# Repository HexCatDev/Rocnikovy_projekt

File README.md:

# Ročníkový projekt S3E Dobeš Tomáš Digitální hodiny
## Zvláštní poděkování
Zvláště bych chtěl poděkovat panu Miroslavu Máchovi za rady a pomoc při výběru součástek a řešení problémů konstrukčního typu.
A také  panu Jiřímu Vinterovi za rady a kontakty.

## To-do list
- [x] Navrhnout schéma 
- [x] Objednat součástky
- [x] Otestovat na breadboardu
- [x] Navrhnout PCB
- [x] Vyrobit PCB osadit, otestovat

## Princip a popis
Původní myšlenka jak zhotovit tento obvod byla, že by se jednotlivé výstupy na zobrazovače připojily přes posuvné registry, ovšem bylo by jich zapotřebí 6 kousků (HH:mm:ss) převod časového údaje z RTC by bylo zhotoveno přímo v PIC.

Po konzultaci s panem Máchou by bylo lepší Multiplexovat číslice 1:6 tzn. že v jednom okamžiku problikne jeden segment, takto se "probliká" každý segment zvlášť v určité rychlosti(Hz), od určité rychlosti ± 30 Hz se obraz jeví jako spojitý.[1]
### Blokové schéma

<figure>
  
  <figcaption align="center"><i>Obrázek 1: Blokové schéma zapojení hodin</i></figcaption>
</figure>

### Součástky a jejich funkce v obvodu
V této podkapitole budou popsány hlavně podstatné součástky RTC, PIC, tranzistorové pole a samotné tranzistory (touto částí obvodu se chápe zobrazovací část. Vzhledem ke složitosti projektu zde nebude popsáno jak každý samostatný prvek funguje. 

- Obecné informace na vstupu napětí jsou  umístěny tzv. Tank Capacitors[2, kap. 4.2.2], jsou to dva kondenzátory 100uF/35V na napájení jejich funkce zajišťuje stabilní napětí při náhlém zvětšení proudového zatížení. Každý IO napájený z VCC má připojený tzv. Decoupling Capacitors[10] tyto kondenzátory mají na starosti odrušení od možných na indukovaných vysokých frekvencí, všechny mají hodnotu 100nF. Dále je v obvodu implementována dioda která obvod chrání před přepólováním její úbytek je ± 1100mV[11], takže velikost napájecího napětí bude 6V (6-1 = 5V) maximální napětí všech IO je 5,5V. Před vyrobením PCB bude zdroj otestován na stabilitu napětí.

- Mozkem obvodu je PIC18F47Q43-I-P[2] má na starosti komunikaci s RTC, multiplexování a řízení hodin. 

- RTC (Real Time Clock)[3] a Krystal[4] 
Tento IO komunikuje pomocí I2C protokolu s PIC a poskytuje časový údaj tento údaj je poskytován v dekadickém formátu. Má také externí zdroj oscilací krystal o frekvenci 32 768 Hz tato hodnota je definovaná v jeho dokumentaci[3, kap. 4.2.1]. Doporučená hodnota kondenzátorů které slouží jako kapacitní zátěž je 20pF.[3, kap. 4.2.1] Kondenzáty byly zapojeny podle doporučeného zapojení v citaci 3 kapitole FIGURE 4-3[3, kap. FIGURE 4-3].

- Tranzistorové pole ULN2804A[5] tento IO ve svém pouzdře DIP 18 obsahuje 8x NPN transistorů se spol. emitorem s max. kolektorovím  proudem 0,5A a max. napětím mezi kolektorem a emitorem 50V tento IO slouží pro výběr segmentu který bude svítit (A-DP)

- 7 Segmentové zobrazovače[6][7] 2x 20,32mm a 2x 10mm se společnou katodou obsahují 16x znaků v pouzdře 2x8 (7+DP) jsou připojeny na přes rezistory na ULN2804A[5] a jednotlivé znaky jsou připojeny přes tranzistory DTA123JCA[8] které uzemňují daný znak.

- tranzistory IRLML5203 SMD[8] P-MOSFET Uds max. 30V Ic 3A P 1.25W tyto tranzistory zajišťují spojení daného segmentu s napětím VCC tzn. pokud bude na 1. digitu svítit znak "A" ULN2804A[5] přivede na pin A napětí a poté tranzistor sepne a tím přivede na anodu proud poteče přes segmenty které jsou uzemněné a v důsledku toho se rozsvítí.

Video: https://youtu.be/Hi3HrBMFoAA

## Návrh schéma a PCB
- návrh schéma byl konzultován s panem Máchou a také byl upravován v souladu s dokumentací jednotlivých součástek s jejich doporučeními.

<figure>
  
  <figcaption align="center"><i>Obr. 1.: Schéma zapojení</i></figcaption>
</figure>

  <figcaption align="center"><i>Obr. 2: Schéma zapojení</i></figcaption>
</figure>

  <figcaption align="center"><i>Obr. 3: Schéma zapojení</i></figcaption>
</figure>

<figure>
  
  <figcaption align="center"><i>Obr. 5: Neosazená PCB deska z horní strany strany</i></figcaption>
</figure>

<figure>
  
  <figcaption align="center"><i>Obrázek 7: Neosazená PCB deska ze spodní strany</i></figcaption>
</figure>

## Komponenty použité v projektu
- Aktivní součástky
	+ MCU https://ecom.cz/eshop/detail/73426-PIC18F47Q43-I-P
	+ RTC https://ecom.cz/eshop/detail/39997-MCP7940M-I-SN
	+ T. pole https://ecom.cz/eshop/detail/5723-ULN2804A
	+ Tranzistory SMD https://ecom.cz/eshop/detail/80941
	+ Dioda SMD https://ecom.cz/eshop/detail/82063-M7-SMD-T-R
- Krystal
	+ Crystal https://www.tme.eu/cz/details/32.768k-38-sr/krystalove-rezonatory-tht/sr-passives/32-768k-3-8-sr/
- Headry:
	+ 2X https://ecom.cz/eshop/detail/84648
	+ 5X https://ecom.cz/eshop/detail/84654
- Patice
	+ SIL 1X5 https://ecom.cz/eshop/detail/85256
  + SIL 1X9 https://ecom.cz/eshop/detail/85261
  + DIP 18 https://ecom.cz/eshop/detail/64634-DIL-18-3-NT-1
  + DIP 40 https://ecom.cz/eshop/detail/64639-DIL-40-6-YT-1
- Zobrazovače
	+ 7 segment 2X 20,32mm: https://ecom.cz/eshop/detail/29807-LD-FYD-8021DUHR-21
	+ 7 segment 10mm: https://ecom.cz/eshop/detail/29798-LD-FYD-3921BUHR-21
- Pasivní součástky
	+ Rezistory a Kondenzátory
		* 4K7 https://ecom.cz/eshop/detail/71624-R1206-4K7-1--WRX
		* 22 pF https://ecom.cz/eshop/detail/53662
		* 100 nF https://ecom.cz/eshop/detail/21330-C1206-0-1UF-X7R-100V-KNCC
		* 470R https://ecom.cz/eshop/detail/71620-R1206-470R-1--WRX
		* 100uF/35V https://ecom.cz/eshop/detail/78716-CERA-100-35-6-3x11-KM
		* 220R https://ecom.cz/eshop/detail/71588
- Svorkovnice https://ecom.cz/eshop/detail/6649-DG126-5-0-02P-14-02
- Tlačítka https://ecom.cz/eshop/detail/55539-T-0670HIM-160G
- Napájecí vidlice (zásuvka) https://ecom.cz/eshop/detail/78223-KNAPZP-25-1610-01
	+ zástrčka https://ecom.cz/eshop/detail/78201-KNAPVK-2514-NES-J-250
## Použitá literatura

- [1] WIKIPEDIA CONTRIBUTORS. *Flicker fusion threshold*. Wikipedia: The Free Encyclopedia [online]. [cit. 2026-01-02]. Dostupné z: https://en.wikipedia.org/wiki/Flicker_fusion_threshold
- [2] MICROCHIP TECHNOLOGY. *PIC18F27/47/57Q43 Data Sheet: 28/40/44/48-Pin, Low-Power, High-Performance Microcontroller with XLP Technology*. 2021. Dostupné z: https://ecom.cz/data/exportdokumentu?soubor=D73426.pdf&nazev=ECOM_73426_PIC18F47Q43-I-P.pdf 
- [3] MICROCHIP TECHNOLOGY. *MCP7940M: Low-Power I2C Real-Time Clock/Calendar with SRAM*. 2012. Dostupné z: https://ecom.cz/data/exportdokumentu?soubor=D39997.pdf&nazev=ECOM_39997_MCP7940M-I-SN.pdf
- [4] SR PASSIVES. *Crystal 32.768kHz: 32.768K-3/8-SR Specification*. Dostupné z: https://www.tme.eu/Document/4ebb629a31bbf93152d2908870dbe0d1/WX2.pdf
- [5] STMICROELECTRONICS. *ULN2801A, ULN2802A, ULN2803A, ULN2804A: Eight Darlington Transistor Arrays*. 2012. Dostupné z: https://ecom.cz/data/exportdokumentu?soubor=D05723.pdf&nazev=ECOM_05723_ULN2804A.pdf
- [6] FORYARD OPTOELECTRONICS. *FYD-8021DUHR-21: Dual Digit 7-Segment Display Specification*. Dostupné z: https://ecom.cz/data/exportdokumentu?soubor=D29806.pdf&nazev=ECOM_29807_LD-FYD-8021DUHR-21.pdf
- [7] FORYARD OPTOELECTRONICS. *FYD-3921BUHR-21: Single Digit 7-Segment Display Specification*. Dostupné z:https://ecom.cz/data/exportdokumentu?soubor=D29797.pdf&nazev=ECOM_29798_LD-FYD-3921BUHR-21.pdf
- [8] 	IRF - Infineon/International Rectifier. *	Tranzistor MFET-P, Uds=30V, Id=3A, P=1.25W, Ron=165mOhm*. Dostupné z: https://ecom.cz/data/exportdokumentu?soubor=D80941.pdf&nazev=ECOM_80941_IRLML5203-SMD.pdf
- [10] WIKIPEDIA CONTRIBUTORS. *Decoupling*. Wikipedia: The Free Encyclopedia [online]. Dostupné z: https://en.wikipedia.org/wiki/Capacitor#Decoupling
- [11] KOME *M7 SMD T/R* Dostupné z: https://www.tme.eu/Document/4a413fd76a83438d5e8f54eb6b2d20d6/m1.pdf

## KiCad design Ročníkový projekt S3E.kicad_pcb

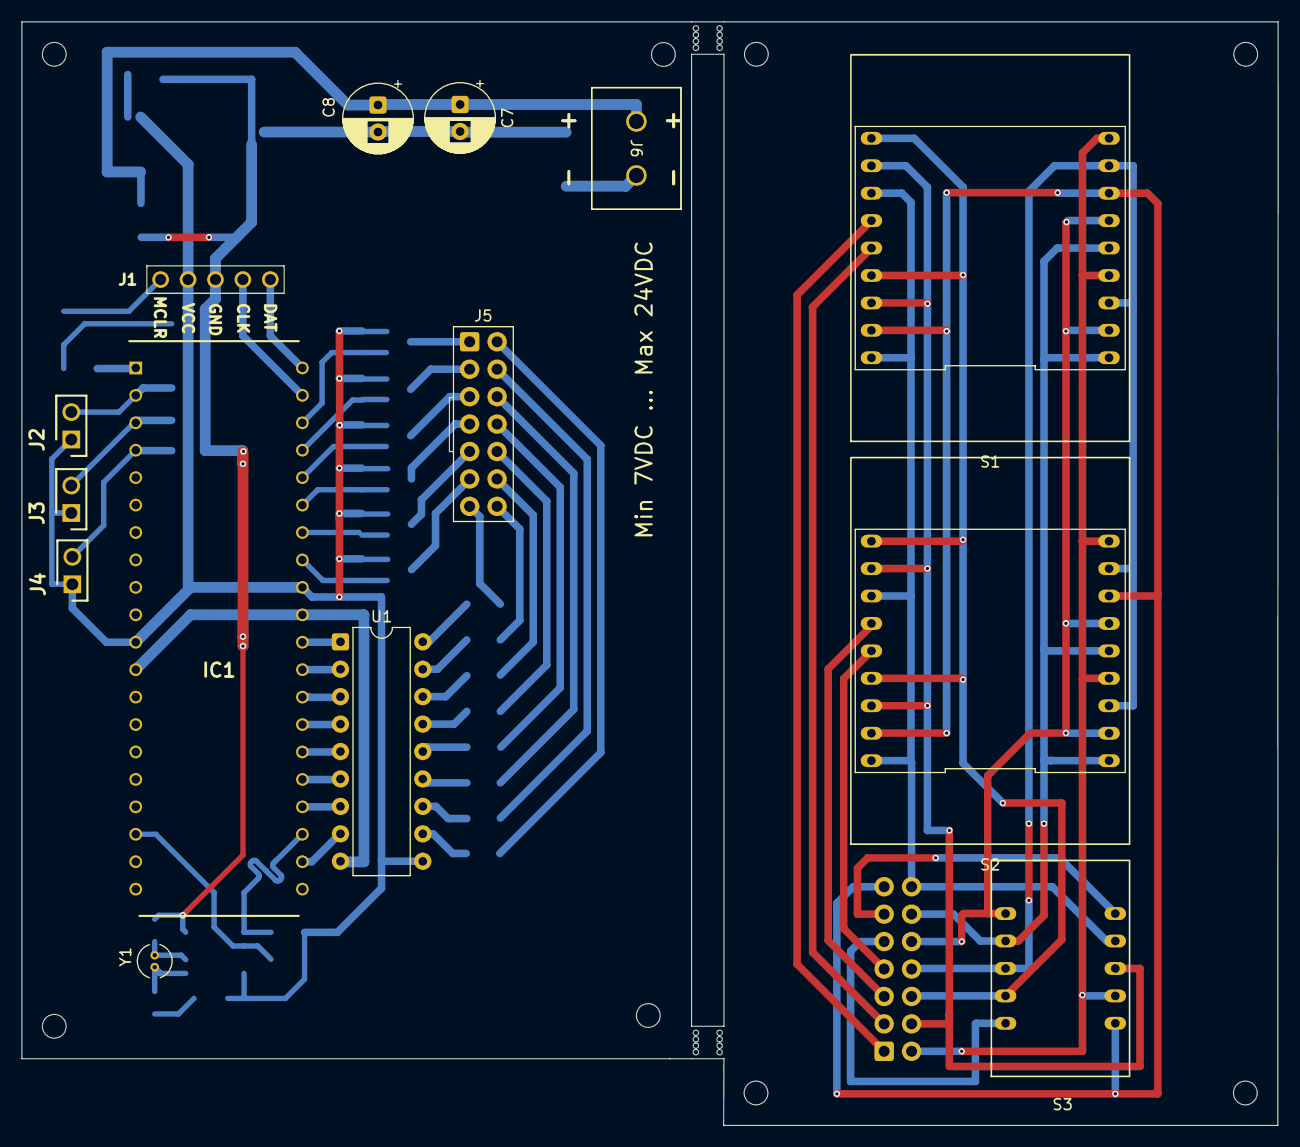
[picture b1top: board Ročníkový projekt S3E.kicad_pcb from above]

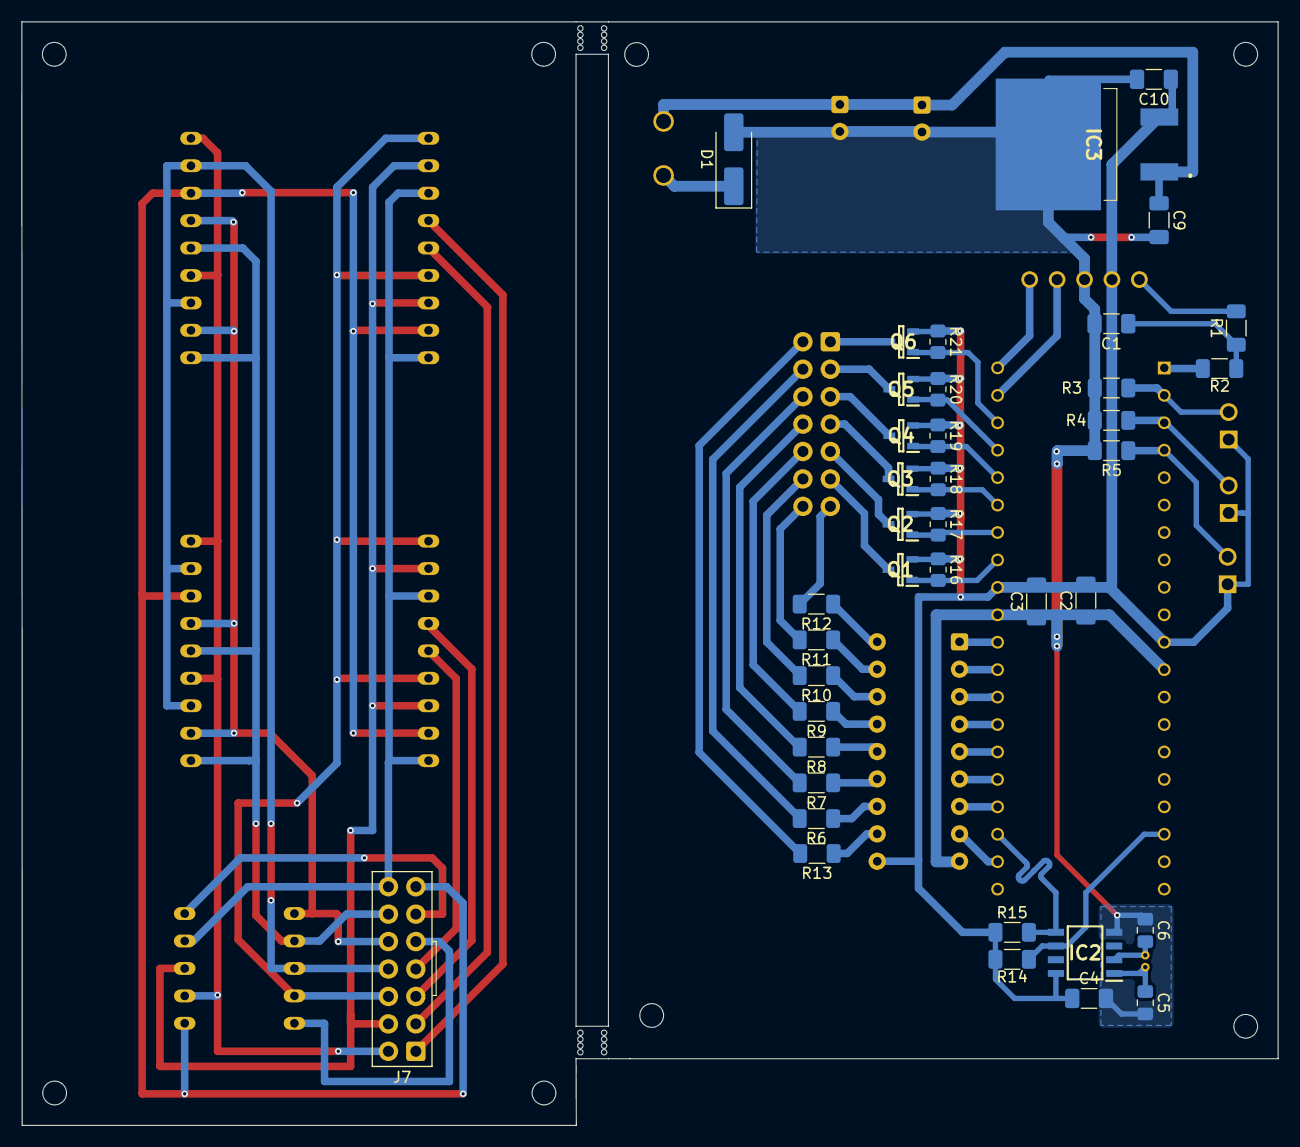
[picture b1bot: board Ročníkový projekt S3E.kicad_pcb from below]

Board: 2 copper layers, 116.3 x 102.2 mm, 59 parts (39 on the bottom side), 52 nets.

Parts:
C1, C2, C3, C4, C9, C10: 100nF; C_1206_3216Metric_Pad1.33x1.80mm_HandSolder
C5, C6: 6,8pF; C_0805_2012Metric_Pad1.18x1.45mm_HandSolder
C7, C8: 100uF; CP_Radial_D6.3mm_P2.50mm
D1: M7 SMD T/R; D_SMA_Handsoldering
H1, H2, H3, H4, H5, H6: MountingHole_2.2mm_M2
IC1: PIC18F47Q43-I_P; DIP1543W58P254L5175H635Q40N
IC2: MCP7940M-I_SN; SOIC127P600X175-8N
IC3: L7805CD2T-TR; L7805CD2T
J1: TSW-105-07-G-S; TSW-105-XX-YY-S
J2, J3, J4: DS1021-1_2SF11-B; HDRV2W64P0X254_1X2_508X254X588P
J5, J7: DIP-14_IDC_2x14
J6: DG126-5.0-02P-14-00A; CONN_DG126-5.0-02P_DEG
Q1, Q2, Q3, Q4, Q5, Q6: YJL2301D; SOT95P240X115-3N
R1, R3, R4, R5, R14, R15: 4K7; R_1206_3216Metric_Pad1.30x1.75mm_HandSolder
R2: 470R; R_1206_3216Metric_Pad1.30x1.75mm_HandSolder
R6, R7, R8, R9, R10, R11, R12, R13: 220R; R_1206_3216Metric_Pad1.30x1.75mm_HandSolder
R16, R17, R18, R19, R20, R21: 10K; R_0805_2012Metric_Pad1.20x1.40mm_HandSolder
S1, S2: DIP 18 Patice Display Digit 1
S3: DIP-10 Patice Display Digit 3 4
U1: ULN2803A; DIP-18_W7.62mm
Y1: 32 768Hz; Crystal_C38-LF_D3.0mm_L8.0mm_Vertical MY 32kHz

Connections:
/A: R6.1, U1.12 (O7)
/A': J5.13, J7.13, R6.2, S1.11 (A), S1.16 (A), S2.11 (A), S2.16 (A), S3.3 (A)
/B: R7.1, U1.13 (O6)
/B': J5.12, J7.12, R7.2, S1.10 (B), S1.15 (B), S2.10 (B), S2.15 (B), S3.9 (B)
/Buttons_board/Button_1: IC1.2 (RA0), J2.2, R3.1
/Buttons_board/Button_2: IC1.3 (RA1), J3.2, R4.1
/Buttons_board/Button_3: IC1.4 (RA2), J4.2, R5.1
/C: R8.1, U1.14 (O5)
/C': J5.11, J7.11, R8.2, S1.3 (C), S1.8 (C), S2.3 (C), S2.8 (C), S3.8 (C)
/D: R9.1, U1.15 (O4)
/D': J5.10, J7.10, R9.2, S1.2 (D), S1.6 (D), S2.2 (D), S2.6 (D), S3.6 (D)
/DP: R13.1, U1.11 (O8)
/DP': J5.14, J7.14, R13.2, S1.4 (DP), S1.9 (DP), S2.4 (DP), S2.9 (DP), S3.2 (DP)
/Display_Board/D1: J5.6, J7.6, Q1.3 (D), S3.5 (Anode2)
/Display_Board/D2: J5.5, J7.5, Q2.3 (D), S3.10 (Anode1)
/Display_Board/D3: J5.4, J7.4, Q3.3 (D), S2.14 (Anode1)
/Display_Board/D4: J5.3, J7.3, Q4.3 (D), S2.13 (Anode2)
/Display_Board/D5: J5.2, J7.2, Q5.3 (D), S1.14 (Anode1)
/Display_Board/D6: J5.1, J7.1, Q6.3 (D), S1.13 (Anode2)
/E: R10.1, U1.16 (O3)
/E': J5.9, J7.9, R10.2, S1.1 (E), S1.5 (E), S2.1 (E), S2.5 (E), S3.7 (E)
/F: R11.1, U1.17 (O2)
/F': J5.8, J7.8, R11.2, S1.12 (F), S1.18 (F), S2.12 (F), S2.18 (F), S3.4 (F)
/G: R12.1, U1.18 (O1)
/G': J5.7, J7.7, R12.2, S1.7 (G), S1.17 (G), S2.7 (G), S2.17 (G), S3.1 (G)
A_1: IC1.33 (RB0), Q1.1 (G), R16.2
A_2: IC1.34 (RB1), Q2.1 (G), R17.2
A_3: IC1.35 (RB2), Q3.1 (G), R18.2
A_4: IC1.36 (RB3), Q4.1 (G), R19.2
A_5: IC1.37 (RB4), Q5.1 (G), R20.2
A_6: IC1.38 (RB5), Q6.1 (G), R21.2
GND: C1.2, C2.1, C3.1, C4.2, C5.2, C6.1, C7.2, C8.2, C9.2, C10.2, D1.2 (A), IC1.12 (VSS_1), IC1.31 (VSS_2), IC2.4 (VSS), IC3.2 (GND), J1.3, R3.2, R4.2, R5.2, U1.9 (GND)
ICSP_CLK: IC1.39 (RB6/ICSPCLK), J1.4
ICSP_DAT: IC1.40 (RB7/ICSPDAT), J1.5
unnamed: C1.1, R1.1, R2.2
unnamed: D1.1 (K), J6.2
unnamed: IC1.1 (~MCLR/VPP/RE3), R2.1
unnamed: C5.1, IC2.1 (X1), Y1.1
unnamed: C6.2, IC2.2 (X2), Y1.2
unnamed: C7.1, C8.1, C9.1, IC3.1 (INPUT), J6.1
unnamed: J1.1, R1.2
PIC_A: IC1.24 (RC5), U1.7 (I7)
PIC_B: IC1.25 (RC6), U1.6 (I6)
PIC_C: IC1.26 (RC7), U1.5 (I5)
PIC_D: IC1.27 (RD4), U1.4 (I4)
PIC_DP: IC1.22 (RD3), U1.8 (I8)
PIC_E: IC1.28 (RD5), U1.3 (I3)
PIC_F: IC1.29 (RD6), U1.2 (I2)
PIC_G: IC1.30 (RD7), U1.1 (I1)
SCL: IC1.18 (RC3), IC2.6 (SCL), R14.2
SDA: IC1.23 (RC4), IC2.5 (SDA), R15.2
VCC: C2.2, C3.2, C4.1, C10.1, IC1.11 (VDD_1), IC1.32 (VDD_2), IC2.8 (VCC), IC3.3 (OUTPUT), J1.2, J2.1, J3.1, J4.1, Q1.2 (S), Q2.2 (S), Q3.2 (S), Q4.2 (S), Q5.2 (S), Q6.2 (S), R14.1, R15.1, R16.1, R17.1, R18.1, R19.1, R20.1, R21.1, U1.10 (COM)

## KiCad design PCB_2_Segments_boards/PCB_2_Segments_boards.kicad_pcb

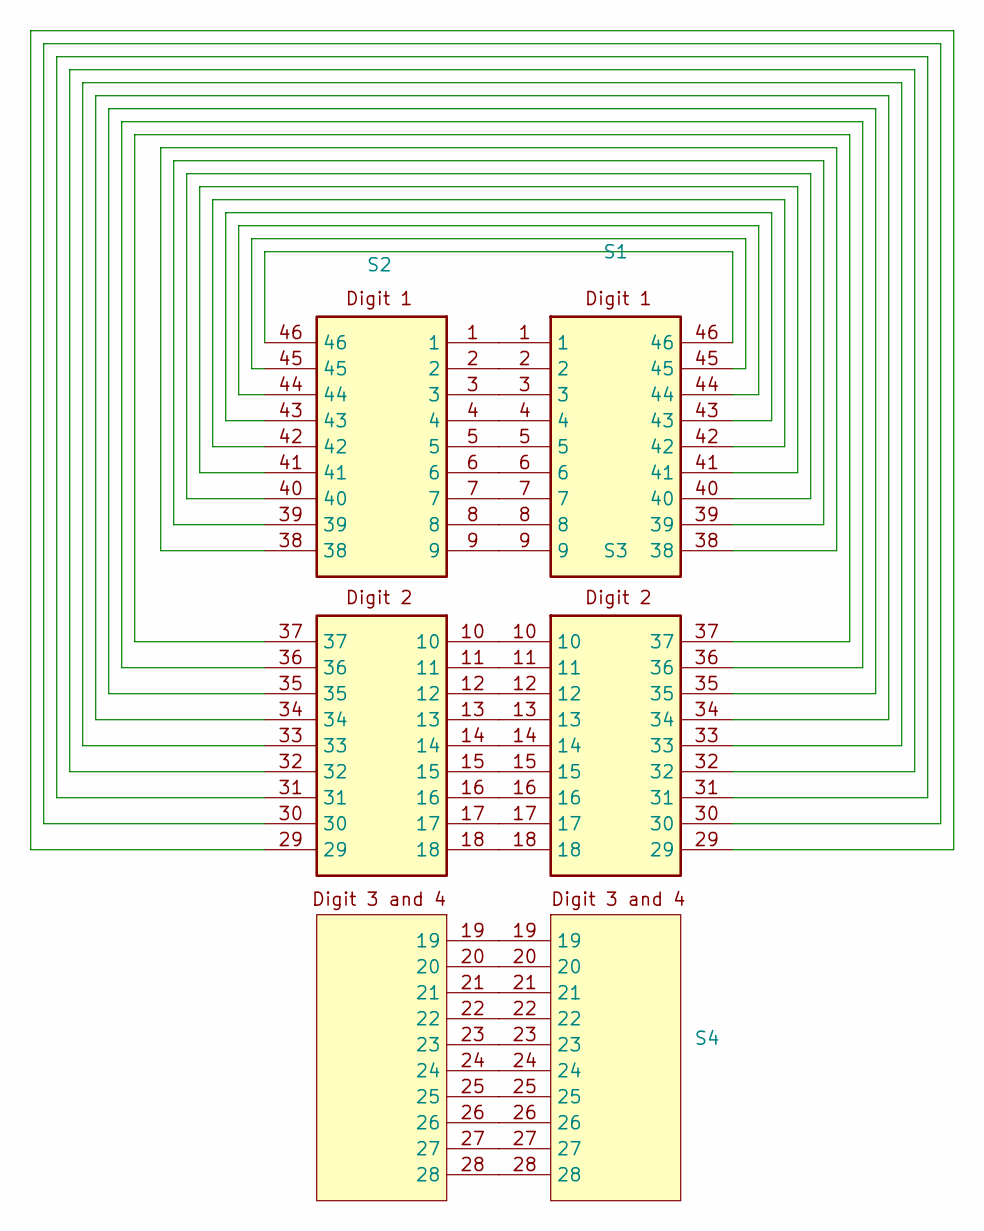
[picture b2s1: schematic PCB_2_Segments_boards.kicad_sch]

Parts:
S1: DIP 18 Patice Display Digit 1
S2: S; Patice_display
S3: DIP 18 Patice Display Digit 2
S4: DIP-10 Patice Display Digit 3 4

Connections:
unnamed: S1.1, S2.1
unnamed: S1.2, S2.2
unnamed: S1.3, S2.3
unnamed: S1.4, S2.4
unnamed: S1.5, S2.5
unnamed: S1.6, S2.6
unnamed: S1.7, S2.7
unnamed: S1.8, S2.8
unnamed: S1.9, S2.9
unnamed: S1.38, S2.38
unnamed: S1.39, S2.39
unnamed: S1.40, S2.40
unnamed: S1.41, S2.41
unnamed: S1.42, S2.42
unnamed: S1.43, S2.43
unnamed: S1.44, S2.44
unnamed: S1.45, S2.45
unnamed: S1.46, S2.46
unnamed: S2.10, S3.10
unnamed: S2.11, S3.11
unnamed: S2.12, S3.12
unnamed: S2.13, S3.13
unnamed: S2.14, S3.14
unnamed: S2.15, S3.15
unnamed: S2.16, S3.16
unnamed: S2.17, S3.17
unnamed: S2.18, S3.18
unnamed: S2.19, S4.19
unnamed: S2.20, S4.20
unnamed: S2.21, S4.21
unnamed: S2.22, S4.22
unnamed: S2.23, S4.23
unnamed: S2.24, S4.24
unnamed: S2.25, S4.25
unnamed: S2.26, S4.26
unnamed: S2.27, S4.27
unnamed: S2.28, S4.28
unnamed: S2.29, S3.29
unnamed: S2.30, S3.30
unnamed: S2.31, S3.31
unnamed: S2.32, S3.32
unnamed: S2.33, S3.33
unnamed: S2.34, S3.34
unnamed: S2.35, S3.35
unnamed: S2.36, S3.36
unnamed: S2.37, S3.37

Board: 2 copper layers, 4 parts (0 on the bottom side), 46 nets, no tracks yet.

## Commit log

2025-12-15 Dokumentace
2025-12-15 README
2025-12-18 Updating readme
2026-01-02 Add LICENSE file with Creative Commons license
2026-01-02 Update documentation and project files
2026-01-02 Move project files to root and add KiCad project
2026-01-02 Citace
2026-01-02 Edit
2026-01-06 backup update
2026-04-13 Auto-backup: 21:43:30 13/04/2026
2026-04-15 Auto-backup: 09:05:42 15/04/2026
2026-04-15 Ignore KiCad local history snapshots
2026-04-17 Auto-backup: 10:53:27 17/04/2026
2026-04-17 Auto-backup: 15:06:39 17/04/2026
2026-04-17 Auto-backup: 15:10:38 17/04/2026
2026-04-17 Auto-backup: 18:09:10 17/04/2026
2026-04-21 Auto-backup: 10:54:24 21/04/2026
2026-05-04 Auto-backup: 22:15:36 04/05/2026
2026-05-04 Auto-backup: 00:14:14 05/05/2026
2026-05-14 Auto-backup: 07:48:27 14/05/2026
2026-05-14 Auto-backup: 14:23:59 14/05/2026
2026-05-14 Auto-backup: 15:05:07 14/05/2026
2026-05-14 Auto-backup: 21:46:07 14/05/2026
2026-05-14 Auto-backup: 21:46:39 14/05/2026
2026-05-20 Auto-backup: 06:50:50 20/05/2026
2026-05-29 Auto-backup: 22:52:14 29/05/2026
2026-06-04 Auto-backup: 12:35:08 04/06/2026
2026-06-09 Auto-backup: 09:34:34 09/06/2026
2026-06-15 Auto-backup: 22:39:23 15/06/2026
